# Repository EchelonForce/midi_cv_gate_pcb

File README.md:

# Eurorack MIDI to 16x16 CV Gate Module

This the KiCAD design of a Eurorack module with 16 CVs and 16 Gate outputs.

Full writeup here: https://www.robotdialogs.com/2022/09/eurorack-midi-to-16x16-cv-gate-module.html

This work is licensed under a Creative Commons Attribution-NonCommercial-ShareAlike 4.0 International License. https://creativecommons.org/licenses/by-nc-sa/4.0/

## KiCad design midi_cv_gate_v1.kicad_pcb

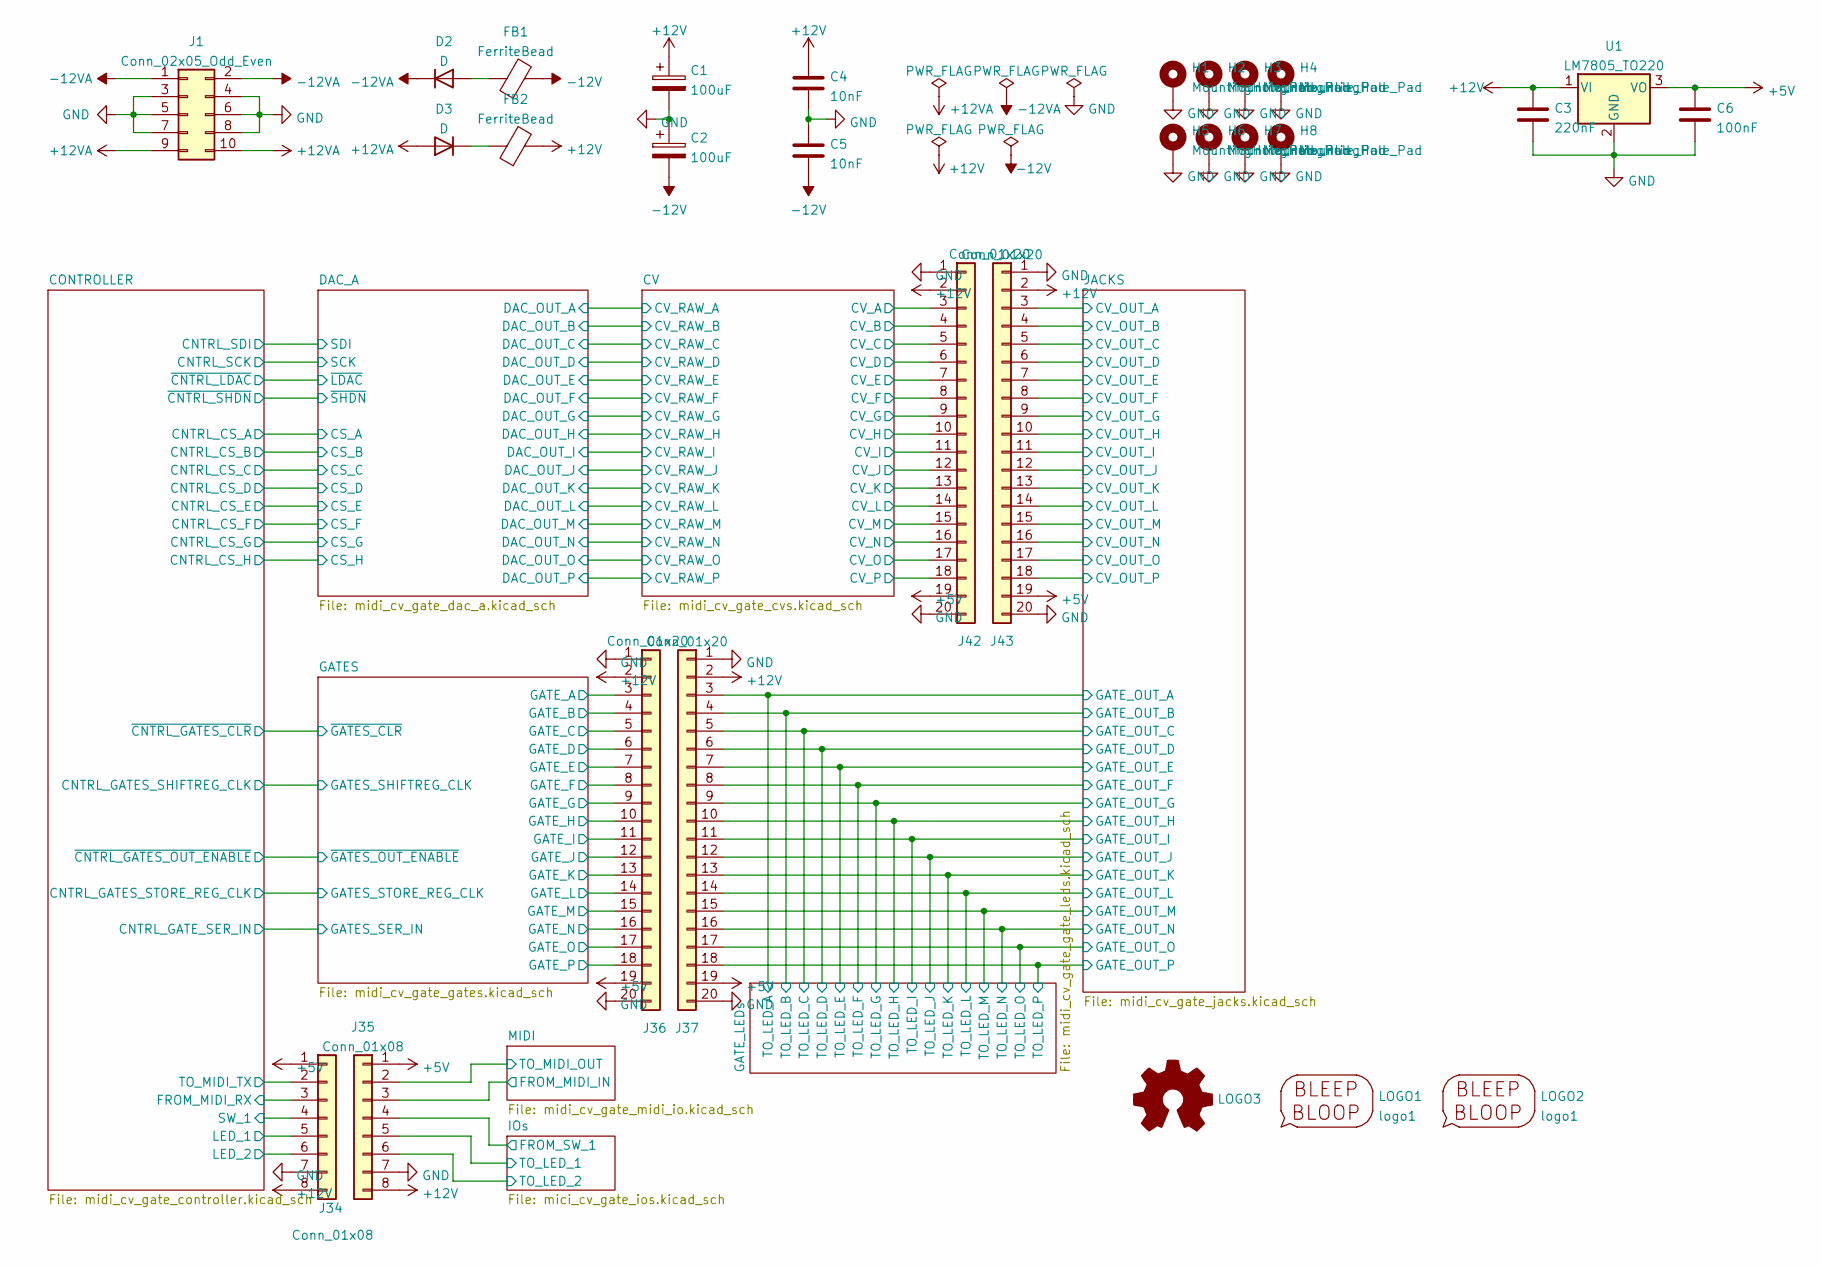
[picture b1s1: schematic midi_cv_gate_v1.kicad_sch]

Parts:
C1, C2: 100uF; CP_Radial_D5.0mm_P2.50mm
C3: 220nF; C_Disc_D4.7mm_W2.5mm_P5.00mm
C4, C5: 10nF; C_Disc_D4.3mm_W1.9mm_P5.00mm
C6: 100nF; C_1206_3216Metric_Pad1.33x1.80mm_HandSolder
D2, D3: D; D_DO-35_SOD27_P7.62mm_Horizontal
FB1, FB2: FerriteBead; L_Axial_L5.3mm_D2.2mm_P7.62mm_Horizontal_Vishay_IM-1
H1, H2, H3, H4, H5, H6, H7, H8: MountingHole_Pad; MountingHole_3.2mm_M3_ISO7380_Pad_TopBottom
J1: Conn_02x05_Odd_Even; IDC-Header_2x05_P2.54mm_Vertical
J34: Conn_01x08; PinHeader_1x09_P2.54mm_Vertical
J35: Conn_01x08; PinSocket_1x08_P2.54mm_Vertical
J36, J42: Conn_01x20; PinHeader_1x20_P2.54mm_Vertical
J37, J43: Conn_01x20; PinSocket_1x20_P2.54mm_Vertical
LOGO1: logo1; Logo1
LOGO2: logo1; Logo2
LOGO3: Logo_Open_Hardware_Small; OSHW-Symbol_6.7x6mm_SilkScreen
U1: LM7805_TO220; TO-220-3_Horizontal_TabDown

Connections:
+5V: C6.1, J34.1, J35.1, J36.19, J37.19, J42.19, J43.19, U1.3 (VO); also elsewhere on the board
+12V: C1.1, C3.1, C4.1, FB2.2, J34.8, J35.8, J36.2, J37.2, J42.2, J43.2, U1.1 (VI); also elsewhere on the board
+12VA: D3.2 (A), J1.9, J1.10
-12V: C2.2, C5.2, FB1.2; also elsewhere on the board
-12VA: D2.1 (K), J1.1, J1.2
/CONTROLLER/FROM_MIDI_RX: J34.3; also elsewhere on the board
/CONTROLLER/LED_1: J34.5; also elsewhere on the board
/CONTROLLER/LED_2: J34.6; also elsewhere on the board
/CONTROLLER/SW_1: J34.4; also elsewhere on the board
/CONTROLLER/TO_MIDI_TX: J34.2; also elsewhere on the board
/CV/CV_A: J42.3; also elsewhere on the board
/CV/CV_B: J42.4; also elsewhere on the board
/CV/CV_C: J42.5; also elsewhere on the board
/CV/CV_D: J42.6; also elsewhere on the board
/CV/CV_E: J42.7; also elsewhere on the board
/CV/CV_F: J42.8; also elsewhere on the board
/CV/CV_G: J42.9; also elsewhere on the board
/CV/CV_H: J42.10; also elsewhere on the board
/CV/CV_I: J42.11; also elsewhere on the board
/CV/CV_J: J42.12; also elsewhere on the board
/CV/CV_K: J42.13; also elsewhere on the board
/CV/CV_L: J42.14; also elsewhere on the board
/CV/CV_M: J42.15; also elsewhere on the board
/CV/CV_N: J42.16; also elsewhere on the board
/CV/CV_O: J42.17; also elsewhere on the board
/CV/CV_P: J42.18; also elsewhere on the board
/GATES/GATE_A: J36.3; also elsewhere on the board
/GATES/GATE_B: J36.4; also elsewhere on the board
/GATES/GATE_C: J36.5; also elsewhere on the board
/GATES/GATE_D: J36.6; also elsewhere on the board
/GATES/GATE_E: J36.7; also elsewhere on the board
/GATES/GATE_F: J36.8; also elsewhere on the board
/GATES/GATE_G: J36.9; also elsewhere on the board
/GATES/GATE_H: J36.10; also elsewhere on the board
/GATES/GATE_I: J36.11; also elsewhere on the board
/GATES/GATE_J: J36.12; also elsewhere on the board
/GATES/GATE_K: J36.13; also elsewhere on the board
/GATES/GATE_L: J36.14; also elsewhere on the board
/GATES/GATE_M: J36.15; also elsewhere on the board
/GATES/GATE_N: J36.16; also elsewhere on the board
/GATES/GATE_O: J36.17; also elsewhere on the board
/GATES/GATE_P: J36.18; also elsewhere on the board
/GATE_LEDs/TO_LED_A: J37.3; also elsewhere on the board
/GATE_LEDs/TO_LED_B: J37.4; also elsewhere on the board
/GATE_LEDs/TO_LED_C: J37.5; also elsewhere on the board
/GATE_LEDs/TO_LED_D: J37.6; also elsewhere on the board
/GATE_LEDs/TO_LED_E: J37.7; also elsewhere on the board
/GATE_LEDs/TO_LED_F: J37.8; also elsewhere on the board
/GATE_LEDs/TO_LED_G: J37.9; also elsewhere on the board
/GATE_LEDs/TO_LED_H: J37.10; also elsewhere on the board
/GATE_LEDs/TO_LED_I: J37.11; also elsewhere on the board
/GATE_LEDs/TO_LED_J: J37.12; also elsewhere on the board
/GATE_LEDs/TO_LED_K: J37.13; also elsewhere on the board
/GATE_LEDs/TO_LED_L: J37.14; also elsewhere on the board
/GATE_LEDs/TO_LED_M: J37.15; also elsewhere on the board
/GATE_LEDs/TO_LED_N: J37.16; also elsewhere on the board
/GATE_LEDs/TO_LED_O: J37.17; also elsewhere on the board
/GATE_LEDs/TO_LED_P: J37.18; also elsewhere on the board
/IOs/FROM_SW_1: J35.4; also elsewhere on the board
/IOs/TO_LED_1: J35.5; also elsewhere on the board
/IOs/TO_LED_2: J35.6; also elsewhere on the board
/JACKS/CV_OUT_A: J43.3; also elsewhere on the board
/JACKS/CV_OUT_B: J43.4; also elsewhere on the board
/JACKS/CV_OUT_C: J43.5; also elsewhere on the board
/JACKS/CV_OUT_D: J43.6; also elsewhere on the board
/JACKS/CV_OUT_E: J43.7; also elsewhere on the board
/JACKS/CV_OUT_F: J43.8; also elsewhere on the board
/JACKS/CV_OUT_G: J43.9; also elsewhere on the board
/JACKS/CV_OUT_H: J43.10; also elsewhere on the board
/JACKS/CV_OUT_I: J43.11; also elsewhere on the board
/JACKS/CV_OUT_J: J43.12; also elsewhere on the board
/JACKS/CV_OUT_K: J43.13; also elsewhere on the board
/JACKS/CV_OUT_L: J43.14; also elsewhere on the board
/JACKS/CV_OUT_M: J43.15; also elsewhere on the board
/JACKS/CV_OUT_N: J43.16; also elsewhere on the board
/JACKS/CV_OUT_O: J43.17; also elsewhere on the board
/JACKS/CV_OUT_P: J43.18; also elsewhere on the board
/MIDI/FROM_MIDI_IN: J35.3; also elsewhere on the board
/MIDI/TO_MIDI_OUT: J35.2; also elsewhere on the board
GND: C1.2, C2.1, C3.2, C4.2, C5.1, C6.2, H1.1, H2.1, H3.1, H4.1, H5.1, H6.1, H7.1, H8.1, J1.3, J1.4, J1.5, J1.6, J1.7, J1.8, J34.7, J35.7, J36.1, J36.20, J37.1, J37.20, J42.1, J42.20, J43.1, J43.20, U1.2 (GND); also elsewhere on the board
unnamed: D2.2 (A), FB1.1
unnamed: D3.1 (K), FB2.1

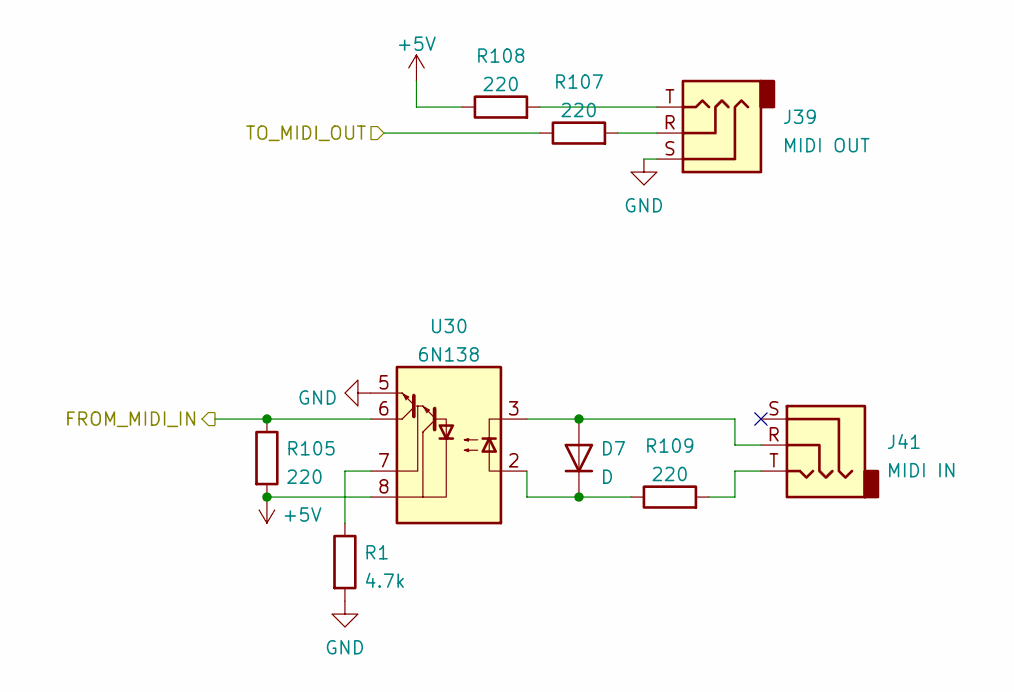
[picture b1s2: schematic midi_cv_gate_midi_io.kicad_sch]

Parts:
D7: D; D_DO-35_SOD27_P7.62mm_Horizontal
J39: MIDI OUT; Jack_3.5mm_MJ-355W_Vertical
J41: MIDI IN; Jack_3.5mm_MJ-355W_Vertical
R1: 4.7k; R_1206_3216Metric_Pad1.30x1.75mm_HandSolder
R105, R107, R108, R109: 220; R_1206_3216Metric_Pad1.30x1.75mm_HandSolder
U30: 6N138; DIP-8_W7.62mm_Socket_LongPads

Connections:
+5V: R105.2, R108.1, U30.8 (VCC); also elsewhere on the board
/MIDI/FROM_MIDI_IN: R105.1, U30.6 (VO2); also elsewhere on the board
/MIDI/TO_MIDI_OUT: R107.1; also elsewhere on the board
GND: J39.S, R1.2, U30.5 (GND); also elsewhere on the board
unnamed: D7.1 (K), R109.1, U30.2 (C1)
unnamed: D7.2 (A), J41.R, U30.3 (C2)
unnamed: J39.R, R107.2
unnamed: J39.T, R108.2
unnamed: J41.T, R109.2
unnamed: R1.1, U30.7 (VO1)

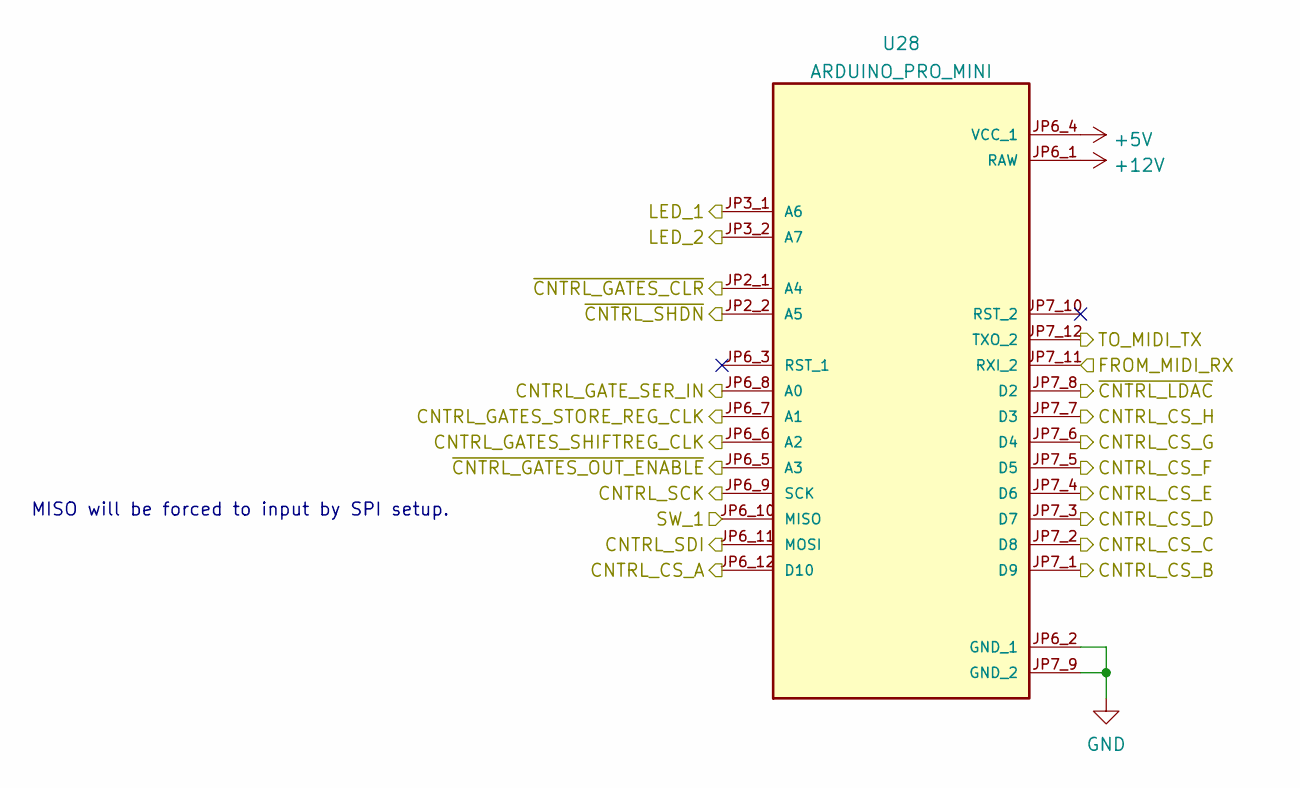
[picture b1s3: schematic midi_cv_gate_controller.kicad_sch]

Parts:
U28: ARDUINO_PRO_MINI; MODULE_ARDUINO_PRO_MINI_custom_2; PARTREV N/A

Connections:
+5V: U28.JP6_4 (VCC_1); also elsewhere on the board
+12V: U28.JP6_1 (RAW); also elsewhere on the board
/CONTROLLER/CNTRL_CS_A: U28.JP6_12 (D10); also elsewhere on the board
/CONTROLLER/CNTRL_CS_B: U28.JP7_1 (D9); also elsewhere on the board
/CONTROLLER/CNTRL_CS_C: U28.JP7_2 (D8); also elsewhere on the board
/CONTROLLER/CNTRL_CS_D: U28.JP7_3 (D7); also elsewhere on the board
/CONTROLLER/CNTRL_CS_E: U28.JP7_4 (D6); also elsewhere on the board
/CONTROLLER/CNTRL_CS_F: U28.JP7_5 (D5); also elsewhere on the board
/CONTROLLER/CNTRL_CS_G: U28.JP7_6 (D4); also elsewhere on the board
/CONTROLLER/CNTRL_CS_H: U28.JP7_7 (D3); also elsewhere on the board
/CONTROLLER/CNTRL_GATES_SHIFTREG_CLK: U28.JP6_6 (A2); also elsewhere on the board
/CONTROLLER/CNTRL_GATES_STORE_REG_CLK: U28.JP6_7 (A1); also elsewhere on the board
/CONTROLLER/CNTRL_GATE_SER_IN: U28.JP6_8 (A0); also elsewhere on the board
/CONTROLLER/CNTRL_SCK: U28.JP6_9 (SCK); also elsewhere on the board
/CONTROLLER/CNTRL_SDI: U28.JP6_11 (MOSI); also elsewhere on the board
/CONTROLLER/FROM_MIDI_RX: U28.JP7_11 (RXI_2); also elsewhere on the board
/CONTROLLER/LED_1: U28.JP3_1 (A6); also elsewhere on the board
/CONTROLLER/LED_2: U28.JP3_2 (A7); also elsewhere on the board
/CONTROLLER/SW_1: U28.JP6_10 (MISO); also elsewhere on the board
/CONTROLLER/TO_MIDI_TX: U28.JP7_12 (TXO_2); also elsewhere on the board
/CONTROLLER/~CNTRL_GATES_CLR: U28.JP2_1 (A4); also elsewhere on the board
/CONTROLLER/~CNTRL_GATES_OUT_ENABLE: U28.JP6_5 (A3); also elsewhere on the board
/CONTROLLER/~CNTRL_LDAC: U28.JP7_8 (D2); also elsewhere on the board
/CONTROLLER/~CNTRL_SHDN: U28.JP2_2 (A5); also elsewhere on the board
GND: U28.JP6_2 (GND_1), U28.JP7_9 (GND_2); also elsewhere on the board

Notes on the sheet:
MISO will be forced to input by SPI setup.

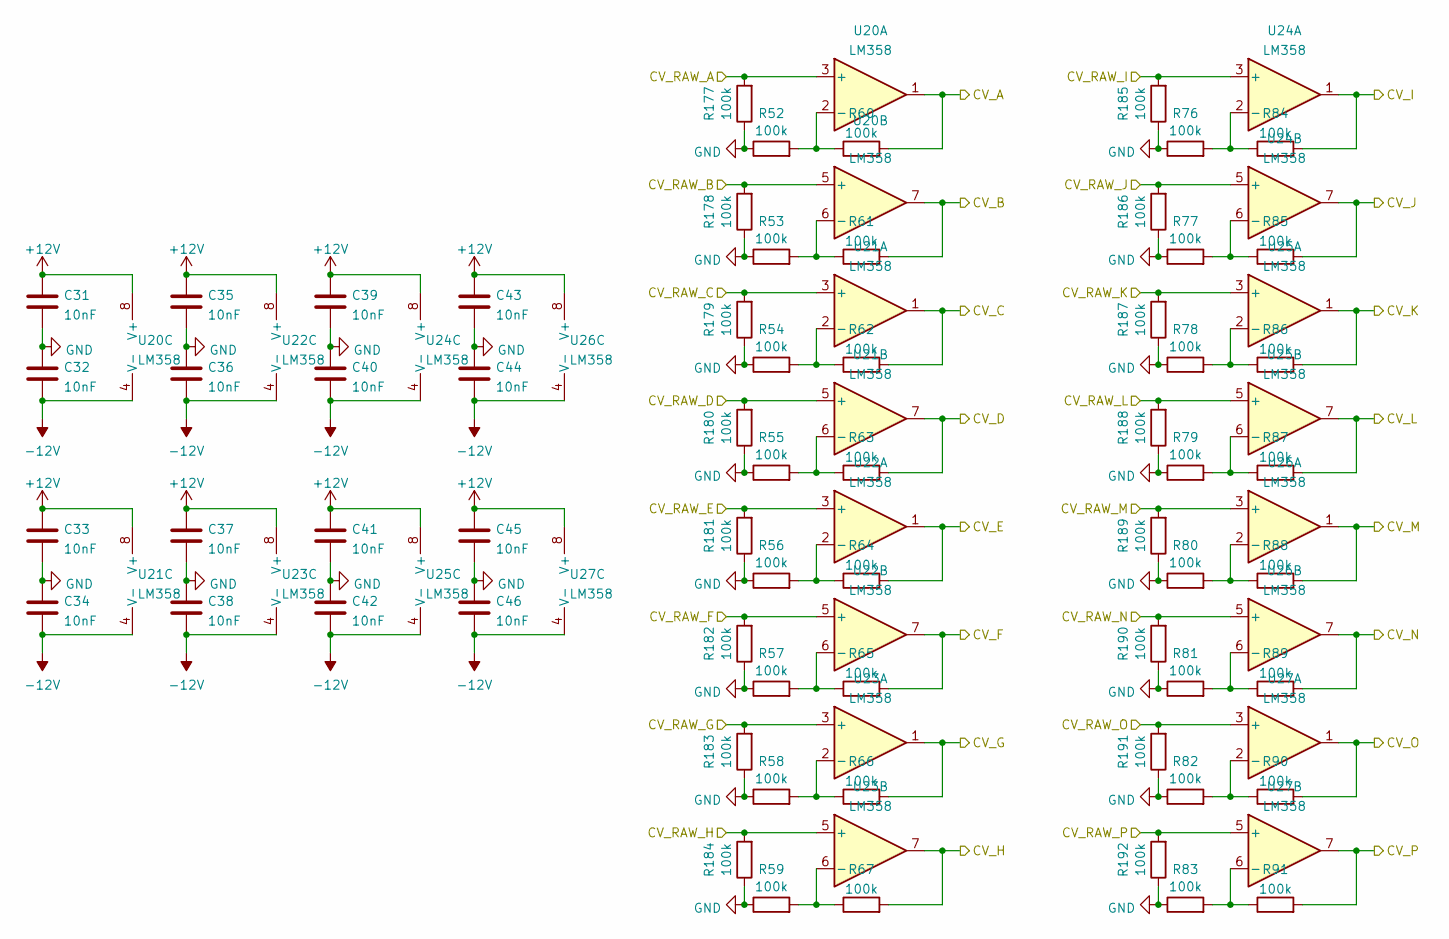
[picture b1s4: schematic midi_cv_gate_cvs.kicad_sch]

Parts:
C31, C32, C33, C34, C35, C36, C37, C38, C39, C40, C41, C42, C43, C44, C45, C46: 10nF; C_1206_3216Metric_Pad1.33x1.80mm_HandSolder
R52, R53, R54, R55, R56, R57, R58, R59, R60, R61, R62, R63, R64, R65, R66, R67, R76, R77, R78, R79, R80, R81, R82, R83, R84, R85, R86, R87, R88, R89, R90, R91, R177, R178, R179, R180, R181, R182, R183, R184, R185, R186, R187, R188, R189, R190, R191, R192: 100k; R_1206_3216Metric_Pad1.30x1.75mm_HandSolder
U20, U21, U22, U23, U24, U25, U26, U27: LM358; DIP-8_W7.62mm_Socket_LongPads

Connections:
+12V: C31.1, C33.1, C35.1, C37.1, C39.1, C41.1, C43.1, C45.1, U20.8 (V+), U21.8 (V+), U22.8 (V+), U23.8 (V+), U24.8 (V+), U25.8 (V+), U26.8 (V+), U27.8 (V+); also elsewhere on the board
-12V: C32.2, C34.2, C36.2, C38.2, C40.2, C42.2, C44.2, C46.2, U20.4 (V-), U21.4 (V-), U22.4 (V-), U23.4 (V-), U24.4 (V-), U25.4 (V-), U26.4 (V-), U27.4 (V-); also elsewhere on the board
/CV/CV_A: R60.2, U20.1; also elsewhere on the board
/CV/CV_B: R61.2, U20.7; also elsewhere on the board
/CV/CV_C: R62.2, U21.1; also elsewhere on the board
/CV/CV_D: R63.2, U21.7; also elsewhere on the board
/CV/CV_E: R64.2, U22.1; also elsewhere on the board
/CV/CV_F: R65.2, U22.7; also elsewhere on the board
/CV/CV_G: R66.2, U23.1; also elsewhere on the board
/CV/CV_H: R67.2, U23.7; also elsewhere on the board
/CV/CV_I: R84.2, U24.1; also elsewhere on the board
/CV/CV_J: R85.2, U24.7; also elsewhere on the board
/CV/CV_K: R86.2, U25.1; also elsewhere on the board
/CV/CV_L: R87.2, U25.7; also elsewhere on the board
/CV/CV_M: R88.2, U26.1; also elsewhere on the board
/CV/CV_N: R89.2, U26.7; also elsewhere on the board
/CV/CV_O: R90.2, U27.1; also elsewhere on the board
/CV/CV_P: R91.2, U27.7; also elsewhere on the board
/CV/CV_RAW_A: R177.2, U20.3 (+); also elsewhere on the board
/CV/CV_RAW_B: R178.2, U20.5 (+); also elsewhere on the board
/CV/CV_RAW_C: R179.2, U21.3 (+); also elsewhere on the board
/CV/CV_RAW_D: R180.2, U21.5 (+); also elsewhere on the board
/CV/CV_RAW_E: R181.2, U22.3 (+); also elsewhere on the board
/CV/CV_RAW_F: R182.2, U22.5 (+); also elsewhere on the board
/CV/CV_RAW_G: R183.2, U23.3 (+); also elsewhere on the board
/CV/CV_RAW_H: R184.2, U23.5 (+); also elsewhere on the board
/CV/CV_RAW_I: R185.2, U24.3 (+); also elsewhere on the board
/CV/CV_RAW_J: R186.2, U24.5 (+); also elsewhere on the board
/CV/CV_RAW_K: R187.2, U25.3 (+); also elsewhere on the board
/CV/CV_RAW_L: R188.2, U25.5 (+); also elsewhere on the board
/CV/CV_RAW_M: R189.2, U26.3 (+); also elsewhere on the board
/CV/CV_RAW_N: R190.2, U26.5 (+); also elsewhere on the board
/CV/CV_RAW_O: R191.2, U27.3 (+); also elsewhere on the board
/CV/CV_RAW_P: R192.2, U27.5 (+); also elsewhere on the board
GND: C31.2, C32.1, C33.2, C34.1, C35.2, C36.1, C37.2, C38.1, C39.2, C40.1, C41.2, C42.1, C43.2, C44.1, C45.2, C46.1, R52.1, R53.1, R54.1, R55.1, R56.1, R57.1, R58.1, R59.1, R76.1, R77.1, R78.1, R79.1, R80.1, R81.1, R82.1, R83.1, R177.1, R178.1, R179.1, R180.1, R181.1, R182.1, R183.1, R184.1, R185.1, R186.1, R187.1, R188.1, R189.1, R190.1, R191.1, R192.1; also elsewhere on the board
unnamed: R52.2, R60.1, U20.2 (-)
unnamed: R53.2, R61.1, U20.6 (-)
unnamed: R54.2, R62.1, U21.2 (-)
unnamed: R55.2, R63.1, U21.6 (-)
unnamed: R56.2, R64.1, U22.2 (-)
unnamed: R57.2, R65.1, U22.6 (-)
unnamed: R58.2, R66.1, U23.2 (-)
unnamed: R59.2, R67.1, U23.6 (-)
unnamed: R76.2, R84.1, U24.2 (-)
unnamed: R77.2, R85.1, U24.6 (-)
unnamed: R78.2, R86.1, U25.2 (-)
unnamed: R79.2, R87.1, U25.6 (-)
unnamed: R80.2, R88.1, U26.2 (-)
unnamed: R81.2, R89.1, U26.6 (-)
unnamed: R82.2, R90.1, U27.2 (-)
unnamed: R83.2, R91.1, U27.6 (-)

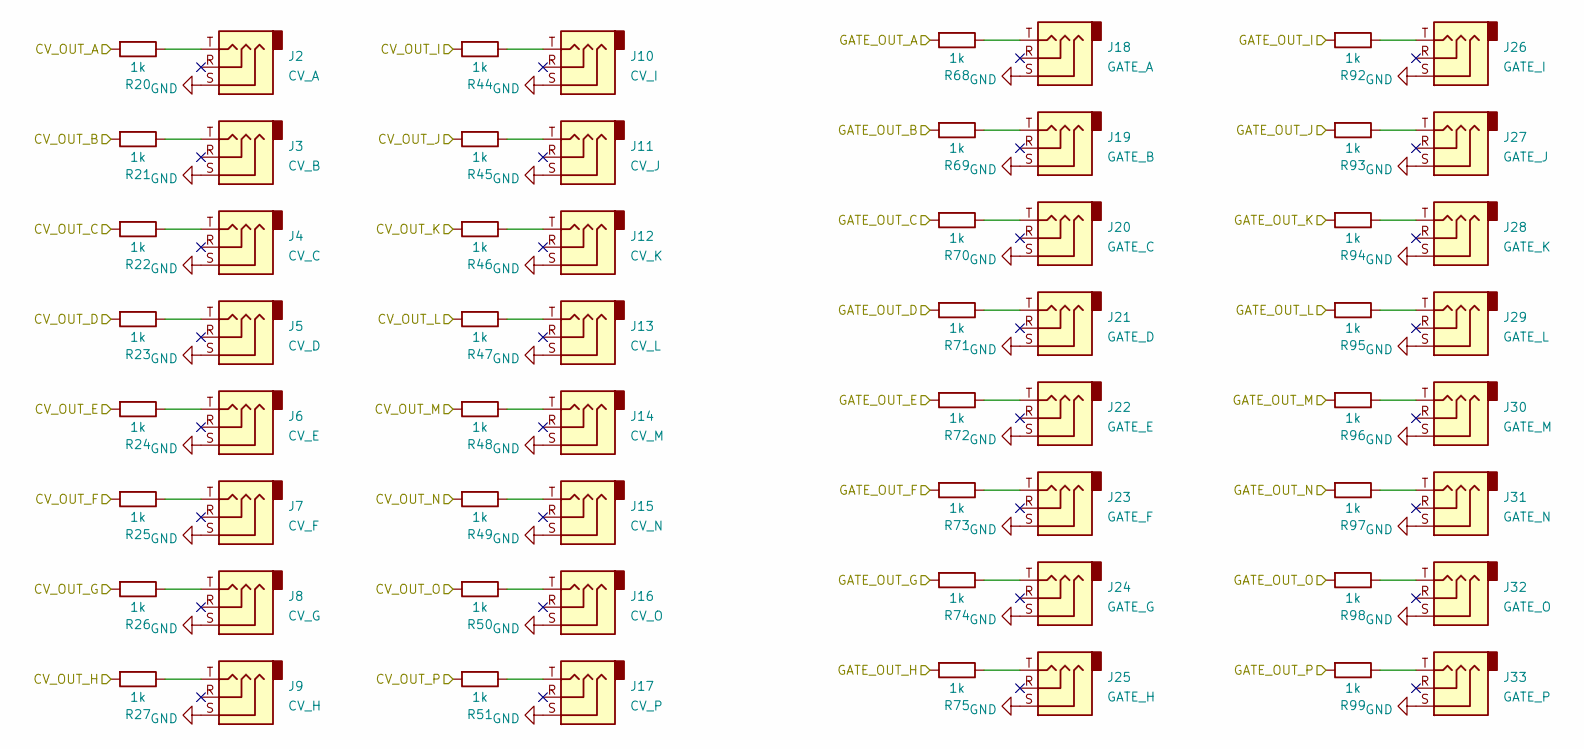
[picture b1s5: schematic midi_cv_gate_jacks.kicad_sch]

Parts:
J2: CV_A; Jack_3.5mm_MJ-355W_Vertical
J3: CV_B; Jack_3.5mm_MJ-355W_Vertical
J4: CV_C; Jack_3.5mm_MJ-355W_Vertical
J5: CV_D; Jack_3.5mm_MJ-355W_Vertical
J6: CV_E; Jack_3.5mm_MJ-355W_Vertical
J7: CV_F; Jack_3.5mm_MJ-355W_Vertical
J8: CV_G; Jack_3.5mm_MJ-355W_Vertical
J9: CV_H; Jack_3.5mm_MJ-355W_Vertical
J10: CV_I; Jack_3.5mm_MJ-355W_Vertical
J11: CV_J; Jack_3.5mm_MJ-355W_Vertical
J12: CV_K; Jack_3.5mm_MJ-355W_Vertical
J13: CV_L; Jack_3.5mm_MJ-355W_Vertical
J14: CV_M; Jack_3.5mm_MJ-355W_Vertical
J15: CV_N; Jack_3.5mm_MJ-355W_Vertical
J16: CV_O; Jack_3.5mm_MJ-355W_Vertical
J17: CV_P; Jack_3.5mm_MJ-355W_Vertical
J18: GATE_A; Jack_3.5mm_MJ-355W_Vertical
J19: GATE_B; Jack_3.5mm_MJ-355W_Vertical
J20: GATE_C; Jack_3.5mm_MJ-355W_Vertical
J21: GATE_D; Jack_3.5mm_MJ-355W_Vertical
J22: GATE_E; Jack_3.5mm_MJ-355W_Vertical
J23: GATE_F; Jack_3.5mm_MJ-355W_Vertical
J24: GATE_G; Jack_3.5mm_MJ-355W_Vertical
J25: GATE_H; Jack_3.5mm_MJ-355W_Vertical
J26: GATE_I; Jack_3.5mm_MJ-355W_Vertical
J27: GATE_J; Jack_3.5mm_MJ-355W_Vertical
J28: GATE_K; Jack_3.5mm_MJ-355W_Vertical
J29: GATE_L; Jack_3.5mm_MJ-355W_Vertical
J30: GATE_M; Jack_3.5mm_MJ-355W_Vertical
J31: GATE_N; Jack_3.5mm_MJ-355W_Vertical
J32: GATE_O; Jack_3.5mm_MJ-355W_Vertical
J33: GATE_P; Jack_3.5mm_MJ-355W_Vertical
R20, R21, R22, R23, R24, R25, R26, R27, R44, R45, R46, R47, R48, R49, R50, R51, R68, R69, R70, R71, R72, R73, R74, R75, R92, R93, R94, R95, R96, R97, R98, R99: 1k; R_1206_3216Metric_Pad1.30x1.75mm_HandSolder

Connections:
/GATE_LEDs/TO_LED_A: R68.2; also elsewhere on the board
/GATE_LEDs/TO_LED_B: R69.2; also elsewhere on the board
/GATE_LEDs/TO_LED_C: R70.2; also elsewhere on the board
/GATE_LEDs/TO_LED_D: R71.2; also elsewhere on the board
/GATE_LEDs/TO_LED_E: R72.2; also elsewhere on the board
/GATE_LEDs/TO_LED_F: R73.2; also elsewhere on the board
/GATE_LEDs/TO_LED_G: R74.2; also elsewhere on the board
/GATE_LEDs/TO_LED_H: R75.2; also elsewhere on the board
/GATE_LEDs/TO_LED_I: R92.2; also elsewhere on the board
/GATE_LEDs/TO_LED_J: R93.2; also elsewhere on the board
/GATE_LEDs/TO_LED_K: R94.2; also elsewhere on the board
/GATE_LEDs/TO_LED_L: R95.2; also elsewhere on the board
/GATE_LEDs/TO_LED_M: R96.2; also elsewhere on the board
/GATE_LEDs/TO_LED_N: R97.2; also elsewhere on the board
/GATE_LEDs/TO_LED_O: R98.2; also elsewhere on the board
/GATE_LEDs/TO_LED_P: R99.2; also elsewhere on the board
/JACKS/CV_OUT_A: R20.2; also elsewhere on the board
/JACKS/CV_OUT_B: R21.2; also elsewhere on the board
/JACKS/CV_OUT_C: R22.2; also elsewhere on the board
/JACKS/CV_OUT_D: R23.2; also elsewhere on the board
/JACKS/CV_OUT_E: R24.2; also elsewhere on the board
/JACKS/CV_OUT_F: R25.2; also elsewhere on the board
/JACKS/CV_OUT_G: R26.2; also elsewhere on the board
/JACKS/CV_OUT_H: R27.2; also elsewhere on the board
/JACKS/CV_OUT_I: R44.2; also elsewhere on the board
/JACKS/CV_OUT_J: R45.2; also elsewhere on the board
/JACKS/CV_OUT_K: R46.2; also elsewhere on the board
/JACKS/CV_OUT_L: R47.2; also elsewhere on the board
/JACKS/CV_OUT_M: R48.2; also elsewhere on the board
/JACKS/CV_OUT_N: R49.2; also elsewhere on the board
/JACKS/CV_OUT_O: R50.2; also elsewhere on the board
/JACKS/CV_OUT_P: R51.2; also elsewhere on the board
GND: J2.S, J3.S, J4.S, J5.S, J6.S, J7.S, J8.S, J9.S, J10.S, J11.S, J12.S, J13.S, J14.S, J15.S, J16.S, J17.S, J18.S, J19.S, J20.S, J21.S, J22.S, J23.S, J24.S, J25.S, J26.S, J27.S, J28.S, J29.S, J30.S, J31.S, J32.S, J33.S; also elsewhere on the board
unnamed: J2.T, R20.1
unnamed: J3.T, R21.1
unnamed: J4.T, R22.1
unnamed: J5.T, R23.1
unnamed: J6.T, R24.1
unnamed: J7.T, R25.1
unnamed: J8.T, R26.1
unnamed: J9.T, R27.1
unnamed: J10.T, R44.1
unnamed: J11.T, R45.1
unnamed: J12.T, R46.1
unnamed: J13.T, R47.1
unnamed: J14.T, R48.1
unnamed: J15.T, R49.1
unnamed: J16.T, R50.1
unnamed: J17.T, R51.1
unnamed: J18.T, R68.1
unnamed: J19.T, R69.1
unnamed: J20.T, R70.1
unnamed: J21.T, R71.1
unnamed: J22.T, R72.1
unnamed: J23.T, R73.1
unnamed: J24.T, R74.1
unnamed: J25.T, R75.1
unnamed: J26.T, R92.1
unnamed: J27.T, R93.1
unnamed: J28.T, R94.1
unnamed: J29.T, R95.1
unnamed: J30.T, R96.1
unnamed: J31.T, R97.1
unnamed: J32.T, R98.1
unnamed: J33.T, R99.1

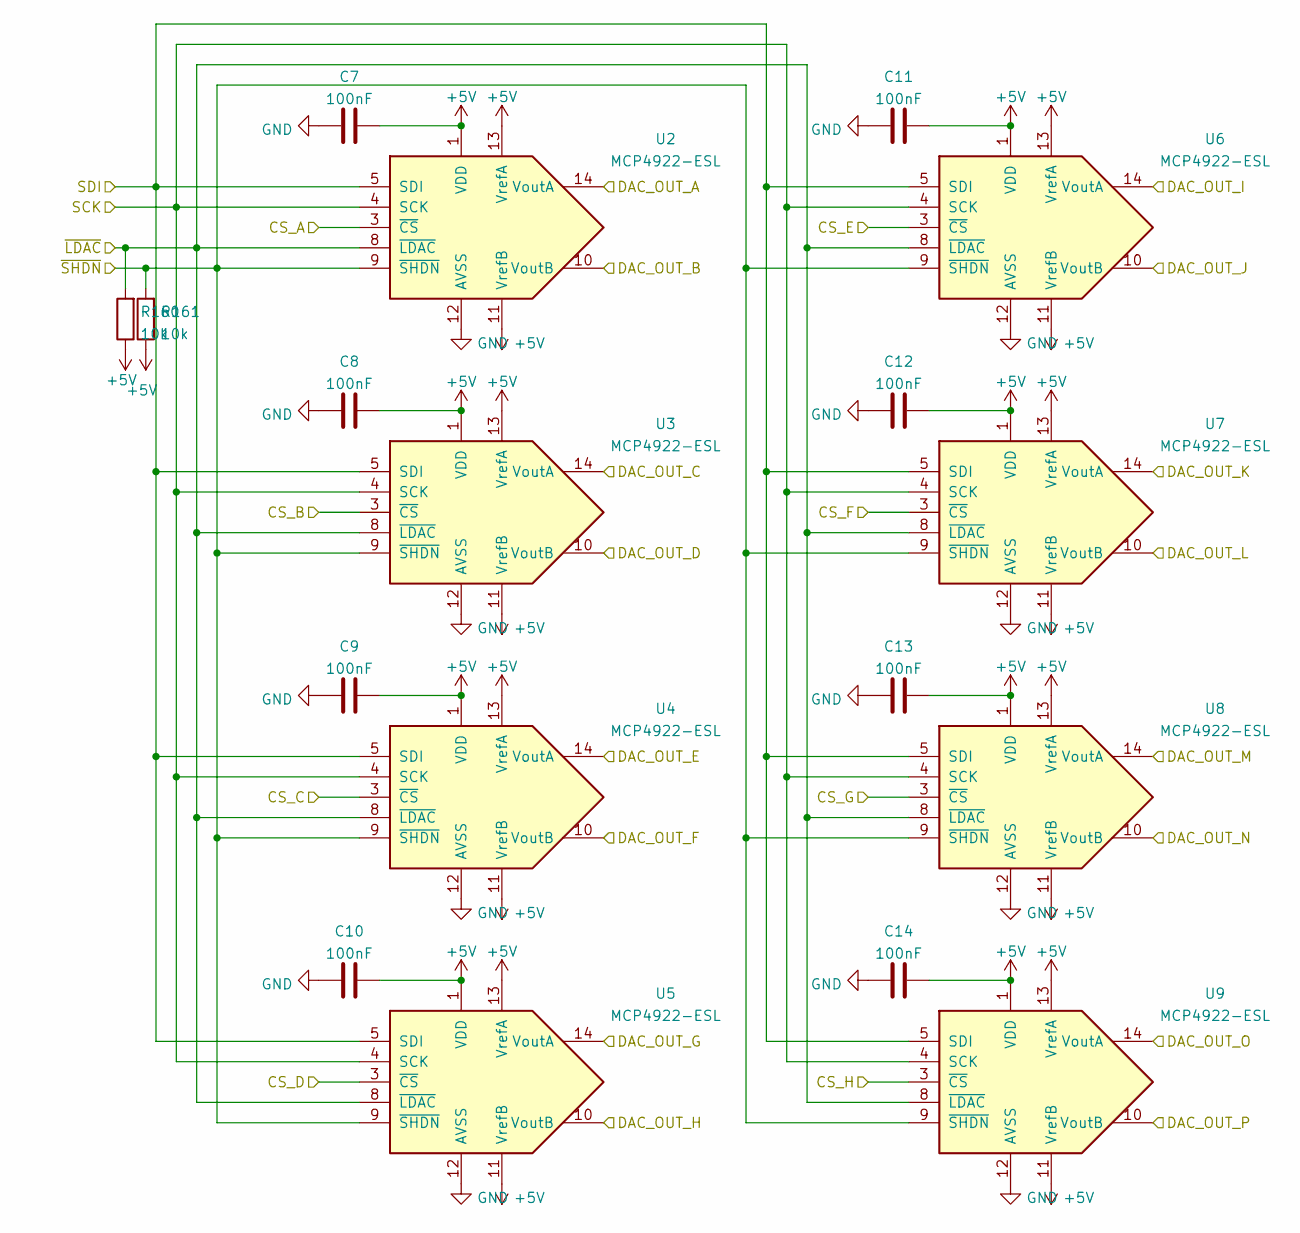
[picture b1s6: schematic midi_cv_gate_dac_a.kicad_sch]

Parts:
C7, C8, C9, C10, C11, C12, C13, C14: 100nF; C_1206_3216Metric_Pad1.33x1.80mm_HandSolder
R160, R161: 10k; R_1206_3216Metric_Pad1.30x1.75mm_HandSolder
U2, U3, U4, U5, U6, U7, U8, U9: MCP4922-ESL; DIP-14_W7.62mm_Socket_LongPads

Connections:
+5V: C7.2, C8.1, C9.2, C10.2, C11.2, C12.2, C13.2, C14.2, R160.1, R161.1, U2.1 (VDD), U2.11 (VrefB), U2.13 (VrefA), U3.1 (VDD), U3.11 (VrefB), U3.13 (VrefA), U4.1 (VDD), U4.11 (VrefB), U4.13 (VrefA), U5.1 (VDD), U5.11 (VrefB), U5.13 (VrefA), U6.1 (VDD), U6.11 (VrefB), U6.13 (VrefA), U7.1 (VDD), U7.11 (VrefB), U7.13 (VrefA), U8.1 (VDD), U8.11 (VrefB), U8.13 (VrefA), U9.1 (VDD), U9.11 (VrefB), U9.13 (VrefA); also elsewhere on the board
/CONTROLLER/CNTRL_CS_A: U2.3 (~CS); also elsewhere on the board
/CONTROLLER/CNTRL_CS_B: U3.3 (~CS); also elsewhere on the board
/CONTROLLER/CNTRL_CS_C: U4.3 (~CS); also elsewhere on the board
/CONTROLLER/CNTRL_CS_D: U5.3 (~CS); also elsewhere on the board
/CONTROLLER/CNTRL_CS_E: U6.3 (~CS); also elsewhere on the board
/CONTROLLER/CNTRL_CS_F: U7.3 (~CS); also elsewhere on the board
/CONTROLLER/CNTRL_CS_G: U8.3 (~CS); also elsewhere on the board
/CONTROLLER/CNTRL_CS_H: U9.3 (~CS); also elsewhere on the board
/CONTROLLER/CNTRL_SCK: U2.4 (SCK), U3.4 (SCK), U4.4 (SCK), U5.4 (SCK), U6.4 (SCK), U7.4 (SCK), U8.4 (SCK), U9.4 (SCK); also elsewhere on the board
/CONTROLLER/CNTRL_SDI: U2.5 (SDI), U3.5 (SDI), U4.5 (SDI), U5.5 (SDI), U6.5 (SDI), U7.5 (SDI), U8.5 (SDI), U9.5 (SDI); also elsewhere on the board
/CONTROLLER/~CNTRL_LDAC: R160.2, U2.8 (~LDAC), U3.8 (~LDAC), U4.8 (~LDAC), U5.8 (~LDAC), U6.8 (~LDAC), U7.8 (~LDAC), U8.8 (~LDAC), U9.8 (~LDAC); also elsewhere on the board
/CONTROLLER/~CNTRL_SHDN: R161.2, U2.9 (~SHDN), U3.9 (~SHDN), U4.9 (~SHDN), U5.9 (~SHDN), U6.9 (~SHDN), U7.9 (~SHDN), U8.9 (~SHDN), U9.9 (~SHDN); also elsewhere on the board
/CV/CV_RAW_A: U2.14 (VoutA); also elsewhere on the board
/CV/CV_RAW_B: U2.10 (VoutB); also elsewhere on the board
/CV/CV_RAW_C: U3.14 (VoutA); also elsewhere on the board
/CV/CV_RAW_D: U3.10 (VoutB); also elsewhere on the board
/CV/CV_RAW_E: U4.14 (VoutA); also elsewhere on the board
/CV/CV_RAW_F: U4.10 (VoutB); also elsewhere on the board
/CV/CV_RAW_G: U5.14 (VoutA); also elsewhere on the board
/CV/CV_RAW_H: U5.10 (VoutB); also elsewhere on the board
/CV/CV_RAW_I: U6.14 (VoutA); also elsewhere on the board
/CV/CV_RAW_J: U6.10 (VoutB); also elsewhere on the board
/CV/CV_RAW_K: U7.14 (VoutA); also elsewhere on the board
/CV/CV_RAW_L: U7.10 (VoutB); also elsewhere on the board
/CV/CV_RAW_M: U8.14 (VoutA); also elsewhere on the board
/CV/CV_RAW_N: U8.10 (VoutB); also elsewhere on the board
/CV/CV_RAW_O: U9.14 (VoutA); also elsewhere on the board
/CV/CV_RAW_P: U9.10 (VoutB); also elsewhere on the board
GND: C7.1, C8.2, C9.1, C10.1, C11.1, C12.1, C13.1, C14.1, U2.12 (AVSS), U3.12 (AVSS), U4.12 (AVSS), U5.12 (AVSS), U6.12 (AVSS), U7.12 (AVSS), U8.12 (AVSS), U9.12 (AVSS); also elsewhere on the board
